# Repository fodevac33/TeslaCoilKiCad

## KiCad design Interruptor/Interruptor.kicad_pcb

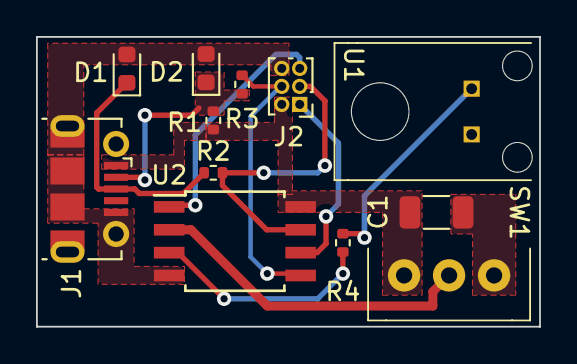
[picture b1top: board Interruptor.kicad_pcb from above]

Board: 2 copper layers, 27.9 x 16.1 mm, 12 parts (0 on the bottom side), 11 nets.

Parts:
C1: 1u; C_1206_3216Metric
D1, D2: D_Zener; D_0603_1608Metric
J1: USB_B_Micro; USB_Micro-B_Molex-105017-0001
J2: Conn_01x06_Pin; PinHeader_2x03_P1.00mm_Vertical
R1: 1.5k; R_0402_1005Metric
R2, R3: 68; R_0402_1005Metric
R4: 100; R_0402_1005Metric
SW1: SW_DPDT_x2; SLW-913535-2A-RA-D
U1: IF-E96E
U2: ATtiny25-20S; SOIC-8W_5.3x5.3mm_P1.27mm

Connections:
+5V: C1.1, J1.1 (VBUS), J2.2, R1.2, SW1.3 (C), U2.8 (VCC)
/MISO: J2.1, U2.6 (PB1)
/MOSI: J2.4, R3.2, U2.5 (AREF/PB0)
/RESET: J2.5, U2.1 (~RESET/PB5)
/SCK: J2.3, R2.2, U2.7 (PB2)
GND: C1.2, D1.2 (A), D2.2 (A), J1.5 (GND), J1.6 (Shield), J2.6, SW1.1 (A), U1.2 (-), U2.4 (GND)
unnamed: D1.1 (K), J1.3 (D+), R2.1
unnamed: D2.1 (K), J1.2 (D-), R1.1, R3.1
unnamed: SW1.2 (B), U2.2 (XTAL1/PB3)
unnamed: R4.1, U1.1 (+)
unnamed: R4.2, U2.3 (XTAL2/PB4)

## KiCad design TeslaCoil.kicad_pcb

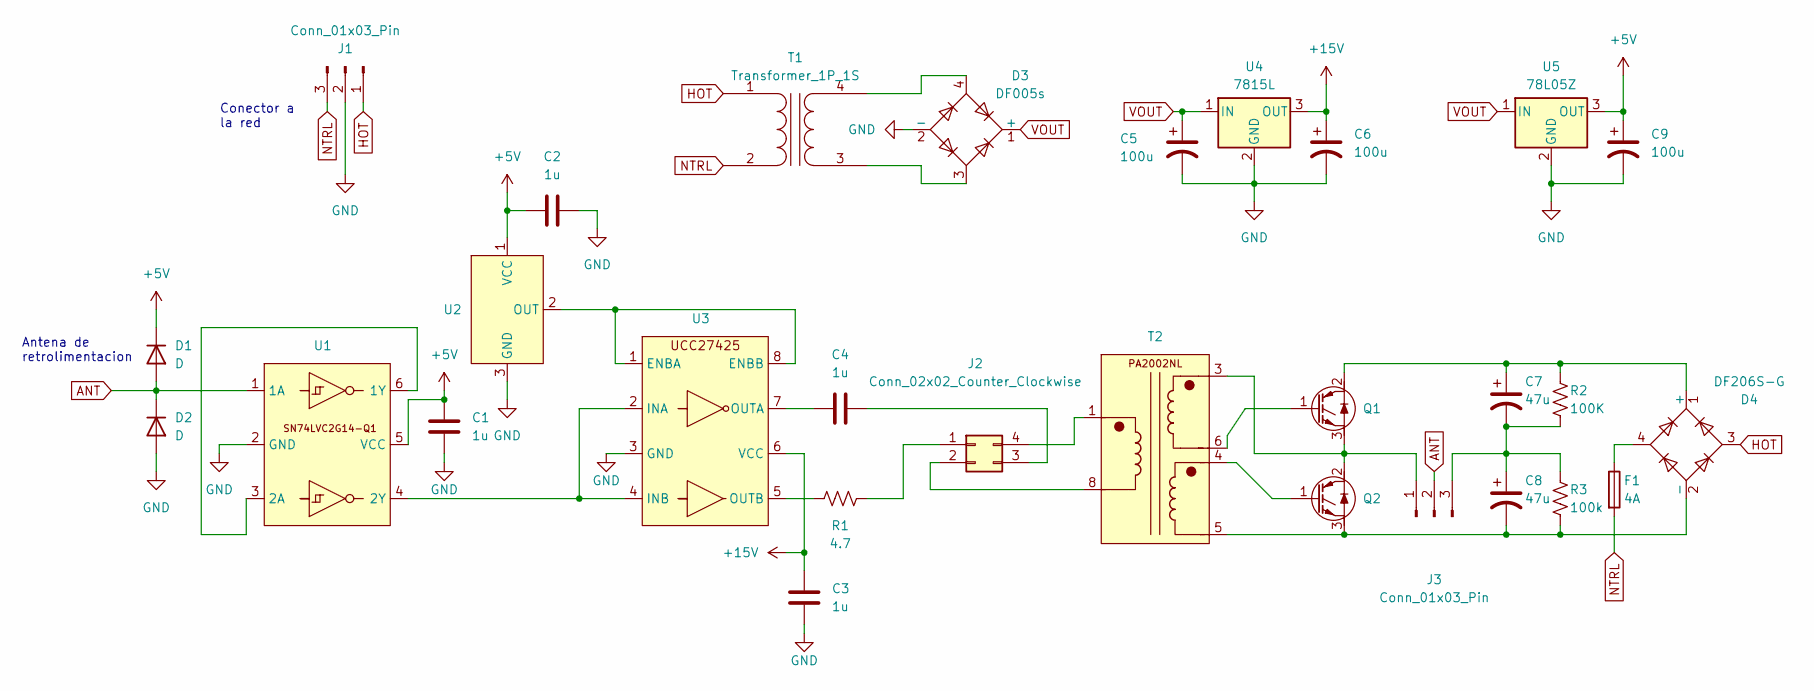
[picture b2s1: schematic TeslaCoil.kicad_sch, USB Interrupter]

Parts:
C1, C2, C3, C4: 1u; C_1206_3216Metric
C5, C6, C9: 100u; C_1206_3216Metric
C7, C8: 47u; CP_Radial_D10.0mm_P5.00mm
D1, D2: D; D_0603_1608Metric
D3: DF005s; Diode_Bridge_Vishay_DFS
D4: DF206S-G; Diode_Bridge_Vishay_DFS
F1: 4A; Fuseholder_Clip-6.3x32mm_Littelfuse_102_122_Inline_P34.21x7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
J1: Conn_01x03_Pin; SolderWire-0.5sqmm_1x03_P4.6mm_D0.9mm_OD2.1mm_Relief
J2: Conn_02x02_Counter_Clockwise; PinHeader_2x02_P1.00mm_Vertical
J3: Conn_01x03_Pin; PinHeader_1x03_P1.00mm_Vertical
Q1, Q2: STGB19NC60KDT4
R1: 4.7; R_0402_1005Metric
R2: 100K; R_0402_1005Metric
R3: 100k; R_0402_1005Metric
T1: Transformer_1P_1S; AS3010-U-0100-120-S
T2: PA2002NL
U1: SN74LVC2G14-Q1
U2: IF-D95T
U3: UCC27425
U4: 7815L; L7805ABD2T-TR
U5: 78L05Z; L7805ABD2T-TR

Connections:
+5V: C1.1, C2.1, C9.1, D1.1 (K), U1.5 (VCC), U2.1 (VCC), U5.3 (OUT)
+15V: C3.1, C6.1, U3.6 (VCC), U4.3 (OUT)
ANT: D1.2 (A), D2.1 (K), J3.2, U1.1 (1A)
GND: C1.2, C2.2, C3.2, C5.2, C6.2, C9.2, D2.2 (A), D3.2 (-), J1.2, U1.2 (GND), U2.3 (GND), U3.3 (GND), U4.2 (GND), U5.2 (GND)
HOT: D4.3, J1.1, T1.1 (AA)
NTRL: F1.2, J1.3, T1.2 (AB)
unnamed: C7.1, D4.1 (+), Q1.2, R2.1
unnamed: C8.2, D4.2 (-), Q2.3, R3.2, T2.5
unnamed: D4.4, F1.1
unnamed: J2.1, R1.2
unnamed: J2.2, T2.8
unnamed: C4.2, J2.3
unnamed: J2.4, T2.1
unnamed: J3.1, Q1.3, Q2.2, T2.3
unnamed: C7.2, C8.1, J3.3, R2.2, R3.1
unnamed: Q1.1, T2.6
unnamed: Q2.1, T2.4
unnamed: D3.3, T1.3 (SA)
unnamed: D3.4, T1.4 (SB)
unnamed: U1.3 (2A), U1.6 (1Y)
unnamed: U1.4 (2Y), U3.2 (INA), U3.4 (INB)
unnamed: U2.2 (OUT), U3.1 (ENBA), U3.8 (ENBB)
unnamed: C4.1, U3.7 (OUTA)
unnamed: R1.1, U3.5 (OUTB)
VOUT: C5.1, D3.1 (+), U4.1 (IN), U5.1 (IN)

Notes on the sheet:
Conector a la red
Antena de retrolimentacion

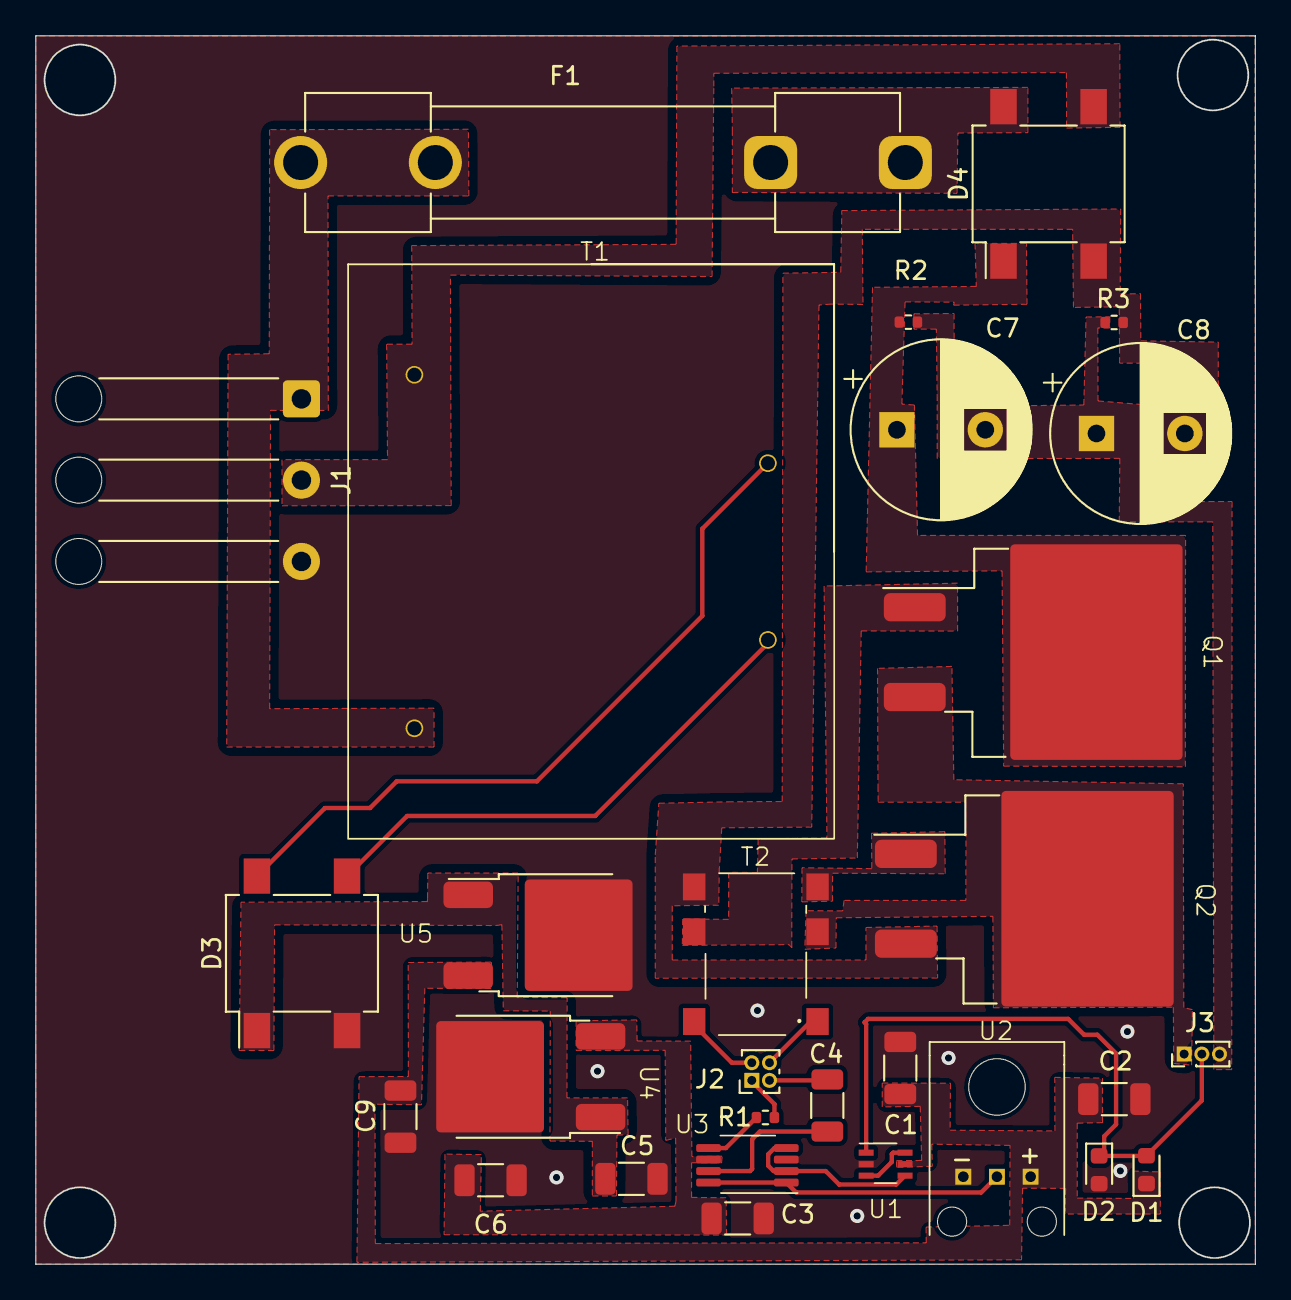
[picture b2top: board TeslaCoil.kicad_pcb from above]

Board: 2 copper layers, 69.0 x 69.5 mm, 29 parts (0 on the bottom side), 25 nets.

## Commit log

2023-11-21 Added footprint library
2023-11-21 Added schematic library
2023-11-23 Interruptor schematic added
2023-11-23 FiberJack added
2023-11-23 Added gitignore, removed backups from version control
2023-11-23 Removed .lck from version control, added extra sheet
2023-11-25 Symbols and references for the switcher squematic
2023-11-25 Added auto files to gitignore
2023-11-26 Finished switching circuit schematic, added txt file for component references
2023-11-26 footprints added
2023-11-26 update references
2023-11-26 New project
2023-11-26 fixed error libraries
2023-11-28 Finished pcb for interruptor circuit
2023-11-28 PCB teslacoil
2023-11-28 fixed errors in merge
2023-11-30 TeslaCoild pcb progress
2023-12-01 Final PCB
2023-12-01 meausures added
2023-12-01 BOM, and Gerber Added
